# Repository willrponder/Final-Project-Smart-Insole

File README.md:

# Smart Insole: Multimodal Sensing for Foot Health Monitoring

## Project Overview

This project aims to develop a smart insole incorporating multimodal sensing to monitor foot health and investigate the detection of diabetic foot ulceration risk.

The system combines photoplethysmography (PPG) and pressure sensing to characterize localized tissue health and mechanical loading across different regions of the foot.

## System Architecture

The proposed system consists of:

- **PPG Sensors:** MAX30101-based sensing modules for collecting localized optical measurements.
- **Pressure Sensors:** Pressure-sensing elements for measuring localized plantar loading.
- **Peripheral Sensor Boards:** Distributed electronics for acquiring data from sensors positioned throughout the insole.
- **Central Controller:** Coordinates sensor communication, data acquisition, and system operation.
- **Communication Interface:** Provides communication between peripheral sensor boards and the central controller.

## Repository Structure

```text
Smart-Insole/
├── Hardware/
│   └── Peripheral-Board/
├── Libraries/
│   ├── Footprints/
│   ├── Symbols/
│   └── 3D-Models/
├── Documentation/
│   ├── Datasheets/
│   ├── Design-Docs/
│   └── Deliverables/
├── Test/
├── README.md
└── .gitignore
```

## Current Development Status

- [ ] Finalize system architecture
- [ ] Complete peripheral board schematic
- [ ] Finalize sensor selection and interfaces
- [ ] Complete PCB layouts
- [ ] Manufacture and assemble prototype boards
- [ ] Develop embedded firmware
- [ ] Integrate sensors into the insole
- [ ] Validate sensing performance

## Design Tools

- **PCB Design:** KiCad
- **Embedded Development:** TBD
- **Version Control:** Git / GitHub

## Documentation

Project documentation, component datasheets, design decisions, and system diagrams are maintained in the `Documentation/` directory.

## Contributors

Project development is currently coordinated through this repository. Contributions and design feedback are welcome.

---

*This is an ongoing research and development project. The system is intended for investigation and prototyping, not as a clinically validated diagnostic device.*

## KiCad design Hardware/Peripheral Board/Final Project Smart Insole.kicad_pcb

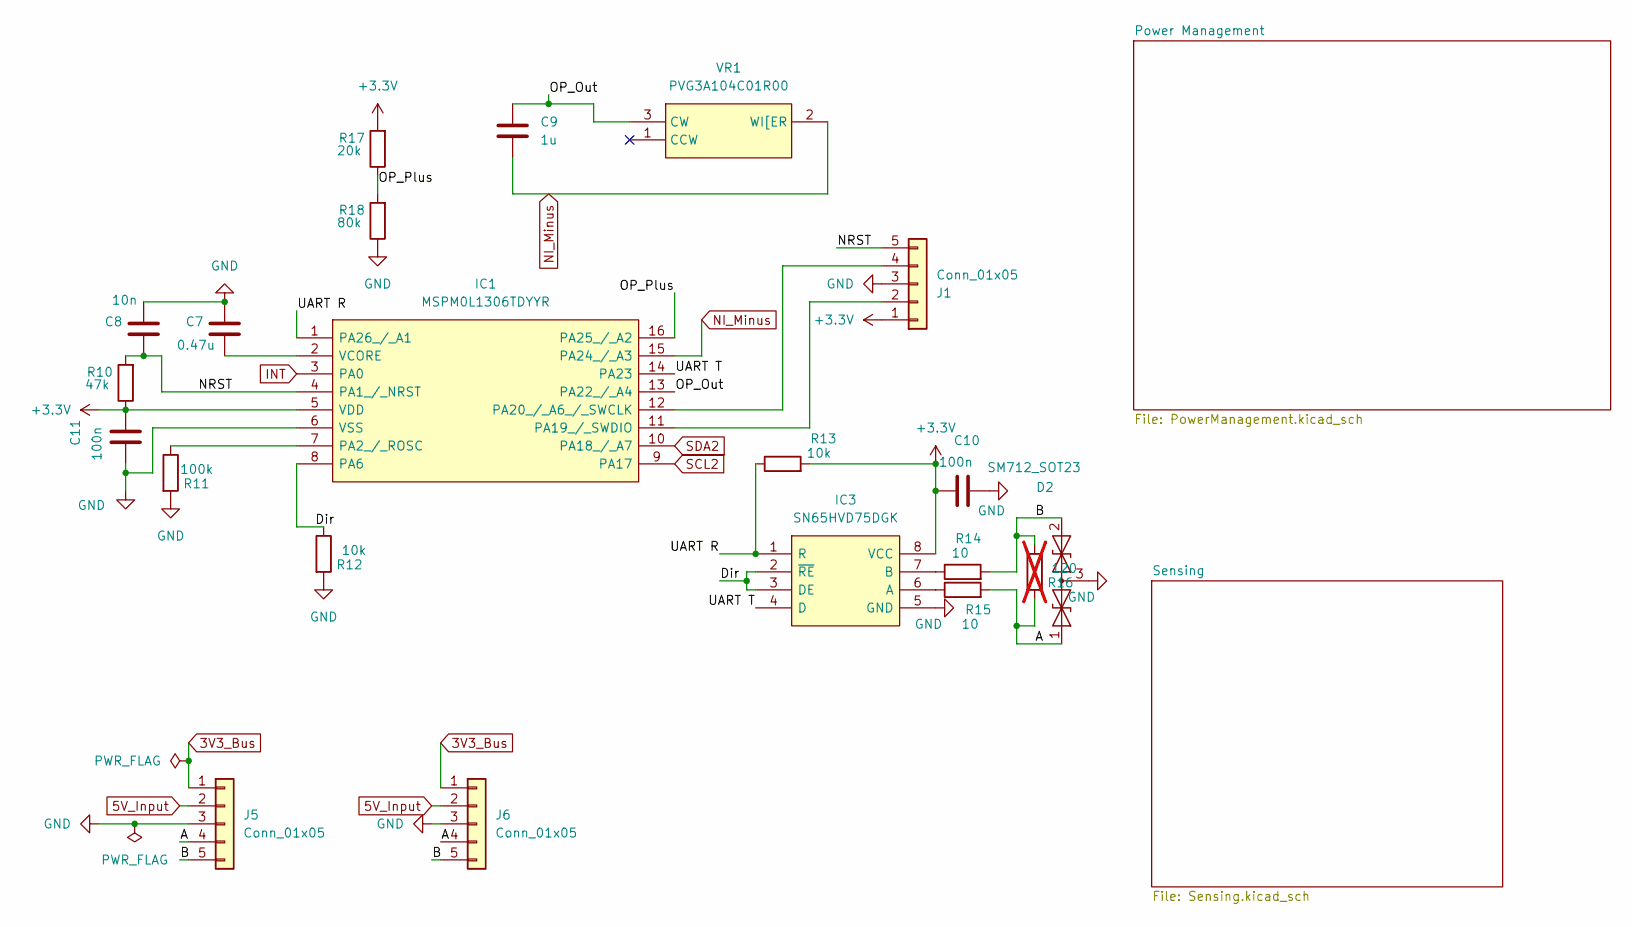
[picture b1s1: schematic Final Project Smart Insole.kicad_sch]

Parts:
C7: 0.47u; C_0402_1005Metric
C8: 10n; C_0402_1005Metric
C9: 1u; C_0402_1005Metric
C10, C11: 100n; C_0402_1005Metric
D2: SM712_SOT23; SOT-23
IC1: MSPM0L1306TDYYR; SOP50P326X110-16N; Mouser Part Number 595-MSPM0L1306TDYYR
IC3: SN65HVD75DGK; SOP65P490X110-8N; Mouser Part Number 595-SN65HVD75DGK
J1, J5, J6: Conn_01x05; PinHeader_1x05_P1.27mm_Vertical
R10: 47k; R_0402_1005Metric
R11: 100k; R_0805_2012Metric
R12, R13: 10k; R_0402_1005Metric
R14, R15: 10; R_0402_1005Metric
R16: 120; R_0402_1005Metric; not fitted
R17: 20k; R_0402_1005Metric
R18: 80k; R_0402_1005Metric
VR1: PVG3A104C01R00

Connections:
3V3_Bus: J5.1, J6.1; also elsewhere on the board
5V_Input: J5.2, J6.2; also elsewhere on the board
+3.3V: C10.1, C11.2, IC1.5 (VDD), IC3.8 (VCC), J1.1, R10.1, R13.2, R17.2; also elsewhere on the board
/A: D2.1 (A1), J5.4, J6.4, R15.2, R16.2
/B: D2.2 (A2), J5.5, J6.5, R14.2, R16.1
/Dir: IC1.8 (PA6), IC3.2 (~RE), IC3.3 (DE), R12.1
/NRST: C8.2, IC1.4 (PA1_/_NRST), J1.5, R10.2
/OP_Out: C9.1, IC1.13 (PA22_/_A4), VR1.3 (CW)
/OP_Plus: IC1.16 (PA25_/_A2), R17.1, R18.2
/UART R: IC1.1 (PA26_/_A1), IC3.1 (R), R13.1
/UART T: IC1.14 (PA23), IC3.4 (D)
GND: C7.1, C8.1, C10.2, C11.1, D2.3 (common), IC1.6 (VSS), IC3.5 (GND), J1.3, J5.3, J6.3, R11.2, R12.2, R18.1; also elsewhere on the board
INT: IC1.3 (PA0); also elsewhere on the board
NI_Minus: C9.2, IC1.15 (PA24_/_A3), VR1.2 (WI[ER); also elsewhere on the board
unnamed: IC1.7 (PA2_/_ROSC), R11.1
unnamed: IC1.11 (PA19_/_SWDIO), J1.2
unnamed: IC1.12 (PA20_/_A6_/_SWCLK), J1.4
unnamed: C7.2, IC1.2 (VCORE)
unnamed: IC3.6 (A), R15.1
unnamed: IC3.7 (B), R14.1
SCL2: IC1.9 (PA17); also elsewhere on the board
SDA2: IC1.10 (PA18_/_A7); also elsewhere on the board

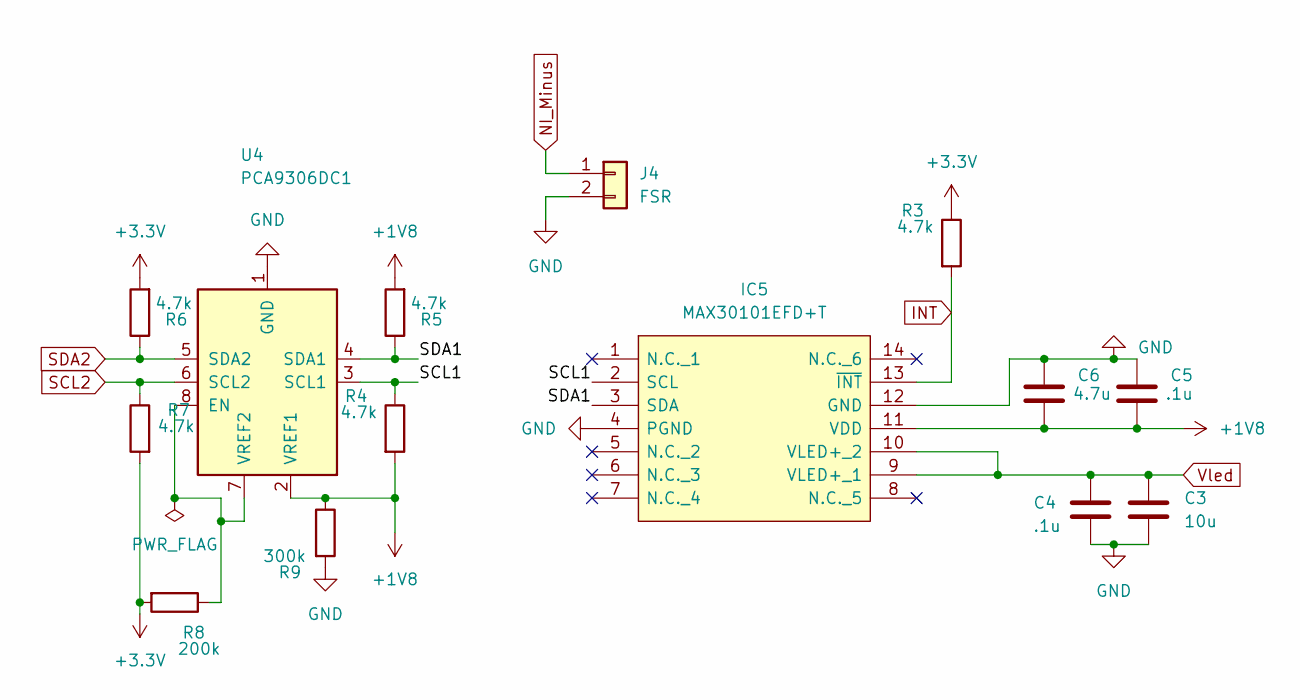
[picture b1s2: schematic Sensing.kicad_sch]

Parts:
C3: 10u; C_0402_1005Metric
C4, C5: .1u; C_0402_1005Metric
C6: 4.7u; C_0402_1005Metric
IC5: MAX30101EFD+T; 14-LEAD-OESIP; Mouser Part Number 700-MAX30101EFD+T
J4: FSR; PinHeader_1x02_P1.27mm_Vertical
R3, R4, R5, R6, R7: 4.7k; R_0402_1005Metric
R8: 200k; R_0402_1005Metric
R9: 300k; R_0402_1005Metric
U4: PCA9306DC1; VSSOP-8_2.3x2mm_P0.5mm

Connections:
+1V8: C5.2, C6.2, IC5.11 (VDD), R4.2, R5.2, R9.1, U4.2 (VREF1); also elsewhere on the board
+3.3V: R3.1, R6.2, R7.2, R8.2; also elsewhere on the board
/Sensing/SCL1: IC5.2 (SCL), R4.1, U4.3 (SCL1)
/Sensing/SDA1: IC5.3 (SDA), R5.1, U4.4 (SDA1)
GND: C3.2, C4.2, C5.1, C6.1, IC5.4 (PGND), IC5.12 (GND), J4.2, R9.2, U4.1 (GND); also elsewhere on the board
INT: IC5.13 (~INT), R3.2; also elsewhere on the board
NI_Minus: J4.1; also elsewhere on the board
unnamed: R8.1, U4.7 (VREF2), U4.8 (EN)
SCL2: R7.1, U4.6 (SCL2); also elsewhere on the board
SDA2: R6.1, U4.5 (SDA2); also elsewhere on the board
Vled: C3.1, C4.1, IC5.9 (VLED+_1), IC5.10 (VLED+_2); also elsewhere on the board

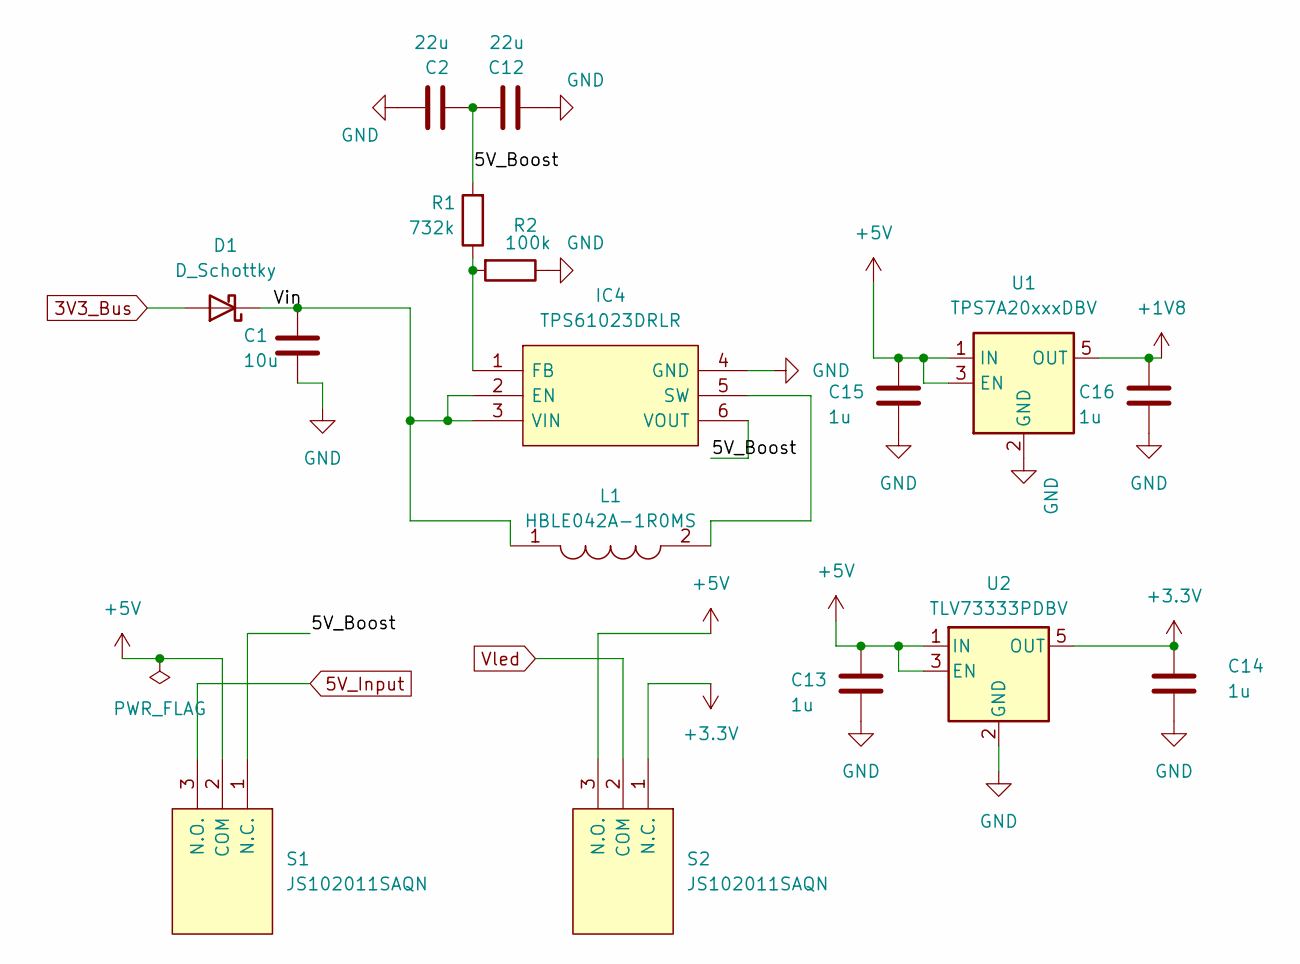
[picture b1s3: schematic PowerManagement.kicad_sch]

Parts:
C1: 10u; C_0402_1005Metric
C2, C12: 22u; C_0402_1005Metric
C13, C14, C15, C16: 1u; C_0402_1005Metric
D1: D_Schottky; D_SOD-123
IC4: TPS61023DRLR; SOTFL50P160X60-6N; Mouser Part Number 595-TPS61023DRLR
L1: HBLE042A-1R0MS; INDM4141X210N
R1: 732k; R_0402_1005Metric
R2: 100k; R_0402_1005Metric
S1, S2: JS102011SAQN
U1: TPS7A20xxxDBV; SOT-23-5
U2: TLV73333PDBV; SOT-23-5

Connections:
3V3_Bus: D1.2 (A); also elsewhere on the board
5V_Input: S1.3 (N.O.); also elsewhere on the board
+1V8: C16.2, U1.5 (OUT); also elsewhere on the board
+3.3V: C14.2, S2.1 (N.C.), U2.5 (OUT); also elsewhere on the board
+5V: C13.2, C15.2, S1.2 (COM), S2.3 (N.O.), U1.1 (IN), U1.3 (EN), U2.1 (IN), U2.3 (EN)
/Power Management/5V_Boost: C2.2, C12.1, IC4.6 (VOUT), R1.2, S1.1 (N.C.)
/Power Management/Vin: C1.1, D1.1 (K), IC4.2 (EN), IC4.3 (VIN), L1.1
GND: C1.2, C2.1, C12.2, C13.1, C14.1, C15.1, C16.1, IC4.4 (GND), R2.1, U1.2 (GND), U2.2 (GND); also elsewhere on the board
unnamed: IC4.1 (FB), R1.1, R2.2
unnamed: IC4.5 (SW), L1.2
Vled: S2.2 (COM); also elsewhere on the board

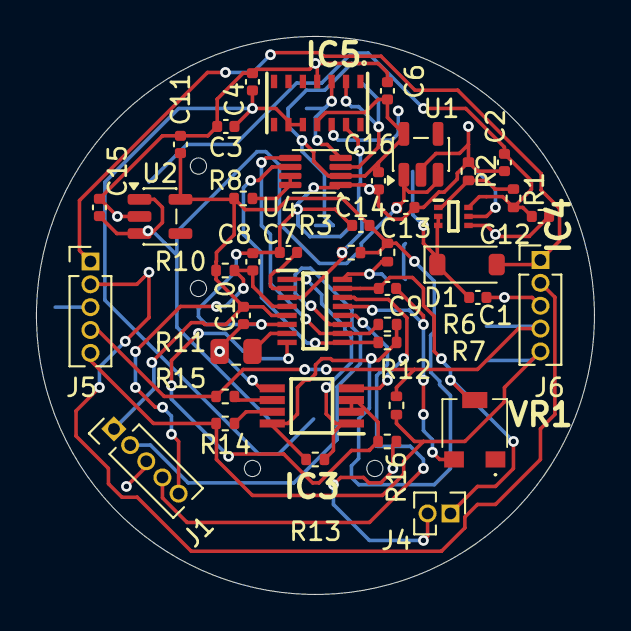
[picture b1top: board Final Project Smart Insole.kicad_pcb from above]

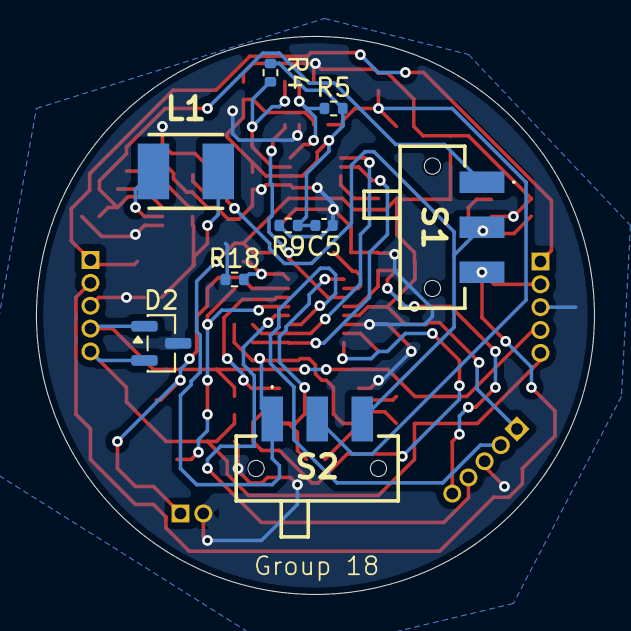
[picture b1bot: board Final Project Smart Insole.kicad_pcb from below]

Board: 2 copper layers, 31.0 x 31.0 mm, 51 parts (9 on the bottom side), 32 nets.
